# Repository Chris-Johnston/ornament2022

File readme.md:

# Xmas Ornament 2022

An ATTiny404 LED Xmas tree ornament. I made a bunch of these as gifts.

## The board

Schematic, in case I don't feel like opening KiCad:

## Resources used

- [svg2mod] was used to generate the footprint of the board, and the front silkscreen layer
  - The Tree Emoji [u1f332] SVG was modified so I could create a footprint from it.
- I referred to [SerialUPDI] to figure out UPDI, but made my own board for adapting between FTDI and UPDI (and left a typo in the name, oops)
- [megaTinyCore] was used with Arduino (via the vscode Arduino extension) to upload to the ATTiny404

[svg2mod]: https://github.com/svg2mod/svg2mod
[u1f332]: https://commons.wikimedia.org/wiki/File:Emoji_u1f332.svg
[SerialUPDI]: https://teddywarner.org/Projects/SerialUPDI/
[megaTinyCore]: https://github.com/SpenceKonde/megaTinyCore

## Bill of Materials

| Reference | Description |
| --------- | ----------- |
| PCB | $0.43 (+ $0.40 shipping) per PCB |
| C1 | 1 uf 1206 capacitor |
| D1 - D7 | 1206 Bidirectional Red/Green LED |
| R1 - R7 | 1206 50 ohm resistor |
| SW1 | 6x6mm Pushbutton |
| SW2 | JS102011SAQN Slide Switch |
| U1 | Attiny404-SS |
| B1 | CR2023 Battery Holder |

## Changes from last year's version

In 2021 I made the [snowflake-ornament], which was a different design that ran on the ATTiny85.
This year I wanted something with a bit more I/O, and it also helps that the ATTiny404 was almost a whole $1 cheaper per unit than the ATTiny85.

Since I had more I/O, I could also fit more LEDs on the board. Instead of only 6 LEDs from last year,
this year's design has 7 bi-directional red/green LEDs. (The ATTiny404 has 6 PWM pins, I wanted PWM on each LED but the design looked weird with only 6.)

One downside of this is that I couldn't use the same programming interfaces that I've used for other boards, but I made my own FTDI to UPDI adapter to handle it.

To connect to the board, instead of leaving an unpopulated programming header, I left some test points and used a spring-loaded pogo pin jig:

Another important change from last year was to use 1206 components everywhere. Last year I used 0603 LEDs, the bigger components were much easier to assemble.

Last year I spent a lot of time optimizing the ornament to run in deep sleep mode when not in use, so I could just use a single button to power it on and change patterns. That was a lot of work, and by the next year the batteries would be dead. This year, I instead just used an on/off switch.

[snowflake-ornament]: https://github.com/Chris-Johnston/snowflake-ornament

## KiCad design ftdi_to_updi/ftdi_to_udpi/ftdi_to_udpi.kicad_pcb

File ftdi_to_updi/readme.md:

# Yes, I know

The folder and footprint should be called "ftdi_to_updi", not "UDPI".

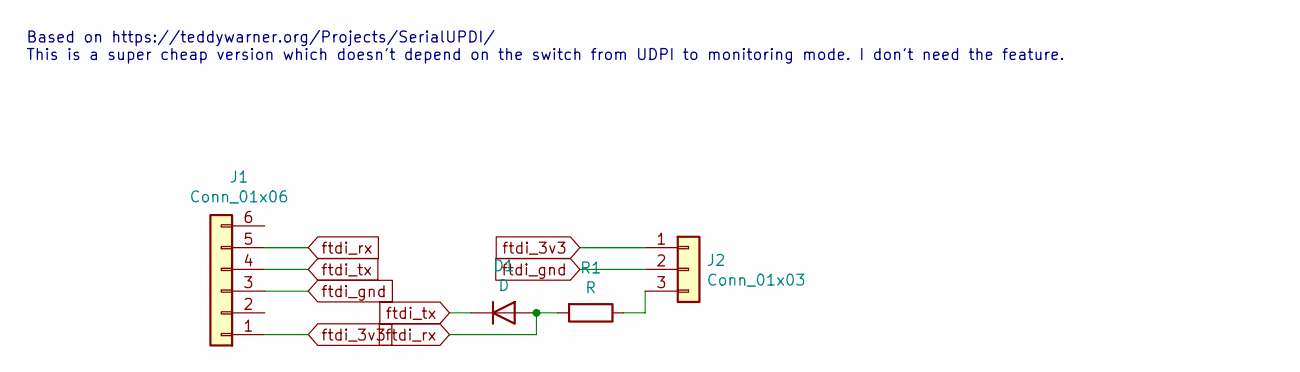
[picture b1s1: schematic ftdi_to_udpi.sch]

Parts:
D1: D; D_T-1_P5.08mm_Horizontal
J1: Conn_01x06; PinHeader_1x06_P2.54mm_Vertical
J2: Conn_01x03; PinHeader_1x03_P2.54mm_Vertical
R1: R; R_Axial_DIN0204_L3.6mm_D1.6mm_P5.08mm_Horizontal

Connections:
unnamed: J2.3, R1.1
ftdi_3v3: J1.1, J2.1
ftdi_gnd: J1.3, J2.2
ftdi_rx: D1.2 (A), J1.5, R1.2
ftdi_tx: D1.1 (K), J1.4

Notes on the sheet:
Based on https://teddywarner.org/Projects/SerialUPDI/ This is a super cheap version which doesn't depend on the switch from UDPI to monitoring mode. I don't need the feature.

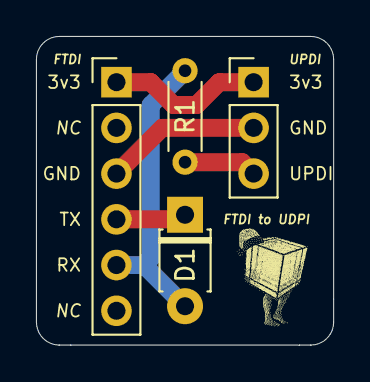
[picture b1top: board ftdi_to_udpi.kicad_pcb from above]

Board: 2 copper layers, 16.5 x 17.1 mm, 4 parts (0 on the bottom side), 5 nets.

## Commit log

2022-12-31 Discard messy history, add files
2022-12-31 add schematic screenshot
2022-12-31 add note about typo
